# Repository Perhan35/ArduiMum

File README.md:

# ArduiMum

An Arduino Mega 2560 project that displays real-time information (bus, time and weather) on a 64x32 RGB LED matrix.

<video src="https://github.com/user-attachments/assets/3b89140a-0723-4620-99fe-7a29e3bc59c3" controls="controls" autoplay="autoplay" loop="loop" muted="muted" style="max-width:100%;">
  Votre navigateur ne supporte pas la lecture de vidéos HTML5.
</video>

## Overview

ArduiMum is an IoT display system that:
- Connects to the internet via an Ethernet shield
- Fetches data from a web API
- Displays weather, time, and other information on an RGB LED matrix
- Syncs time using NTP (Network Time Protocol)

## Demo

### Video
<video src="https://github.com/user-attachments/assets/1bf52050-51cb-4c1d-a350-9c1a7baf006a" controls="controls" autoplay="autoplay" loop="loop" muted="muted" style="max-width:100%;">
  Your browser does not support HTML5 video.
</video>

### Photos

## Hardware

- **Microcontroller:** Arduino Mega 2560
- **Display:** RGB LED Matrix (16x32 or similar)
- **Network:** Ethernet Shield
- **Schematics:** Available in the `MumBoard/` directory (Eagle format)

## Getting Started

1. Install [Arduino IDE](https://www.arduino.cc/en/software)
2. Install required libraries through Arduino IDE:
   - RGB matrix Panel by Adafruit
   - Adafruit GFX Library by Adafruit
   - Time by Michael Margolis
3. Set board to "Arduino Mega 2560"
4. Load `projetMum/projetMum.ino` and upload to the board

## Project Structure

- `projetMum/` — Main Arduino sketch and configuration
- `MumBoard/` — Hardware schematics and PCB design files
- `libraries/` — Custom and third-party libraries
- `pictures/` — Reference images and documentation

## License

Copyright © Perhan Scudeller

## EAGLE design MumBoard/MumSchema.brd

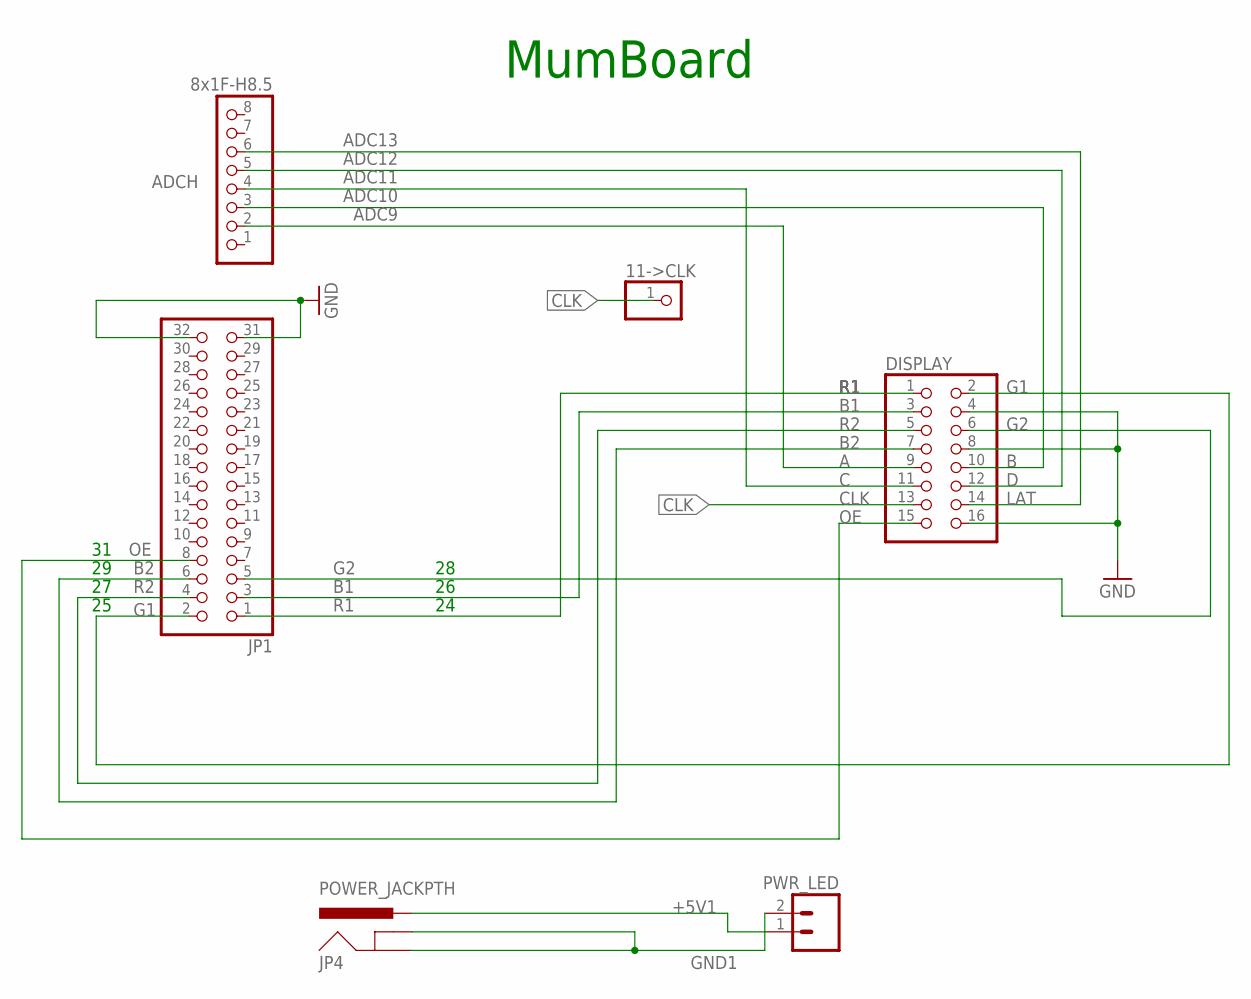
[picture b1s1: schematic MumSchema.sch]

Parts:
11->CLK: PINHD-1X1; 1X01
ADCH: 8x1F-H8.5; 1X08
DISPLAY: PINHD-2X8; 2X08
JP1: PINHD-2X16; 2X16
JP4: POWER_JACKPTH; POWER_JACK_PTH
PWR_LED: M023.5MM; SCREWTERMINAL-3.5MM-2

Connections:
+5V1: JP4.PWR, PWR_LED.1
A: ADCH.2, DISPLAY.9
B: ADCH.3, DISPLAY.10
B1: DISPLAY.3, JP1.3
B2: DISPLAY.7, JP1.6
C: ADCH.4, DISPLAY.11
CLK: 11->CLK.1, DISPLAY.13
D: ADCH.5, DISPLAY.12
G1: DISPLAY.2, JP1.2
G2: DISPLAY.6, JP1.5
GND: DISPLAY.4, DISPLAY.8, DISPLAY.16, JP1.31, JP1.32
GND1: JP4.GND, JP4.GNDBREAK, PWR_LED.2
LAT: ADCH.6, DISPLAY.14
OE: DISPLAY.15, JP1.8
R1: DISPLAY.1, JP1.1
R2: DISPLAY.5, JP1.4

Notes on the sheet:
MumBoard

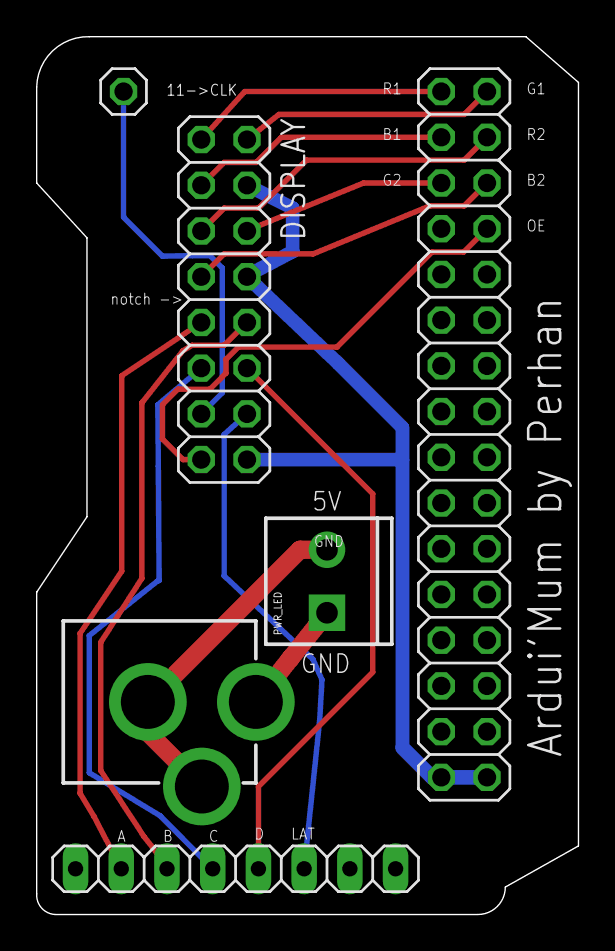
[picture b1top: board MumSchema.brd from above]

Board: 2 copper layers, 30.1 x 48.8 mm, 6 parts (0 on the bottom side), 16 nets.

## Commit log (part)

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2019-12-31 added rainForecast, and some fixes
2019-12-31 perenthesis missing & fixed webpage
2020-01-10 updated doc with rain & updateTime
2020-01-13 homemade EAGLE schema for board & LED Matrix connection
2020-01-14 files description added
2020-01-15 added some pictures of the LED Matrix
2020-05-08 comment added
2024-12-30 feat: new bus logo and new weather API
2026-04-30 feat: add initial README.md with project overview and setup instructions
2026-04-30 feat: add demo section with video and images to README.md
2026-04-30 fix: update video source URL in README.md for demo section
2026-04-30 fix: update video source URL in demo section of README.md

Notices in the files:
parts and their libraries:
SparkFun-Connectors: Licensing: Creative Commons ShareAlike 4.0 International - https://creativecommons.org/licenses/by-sa/4.0
